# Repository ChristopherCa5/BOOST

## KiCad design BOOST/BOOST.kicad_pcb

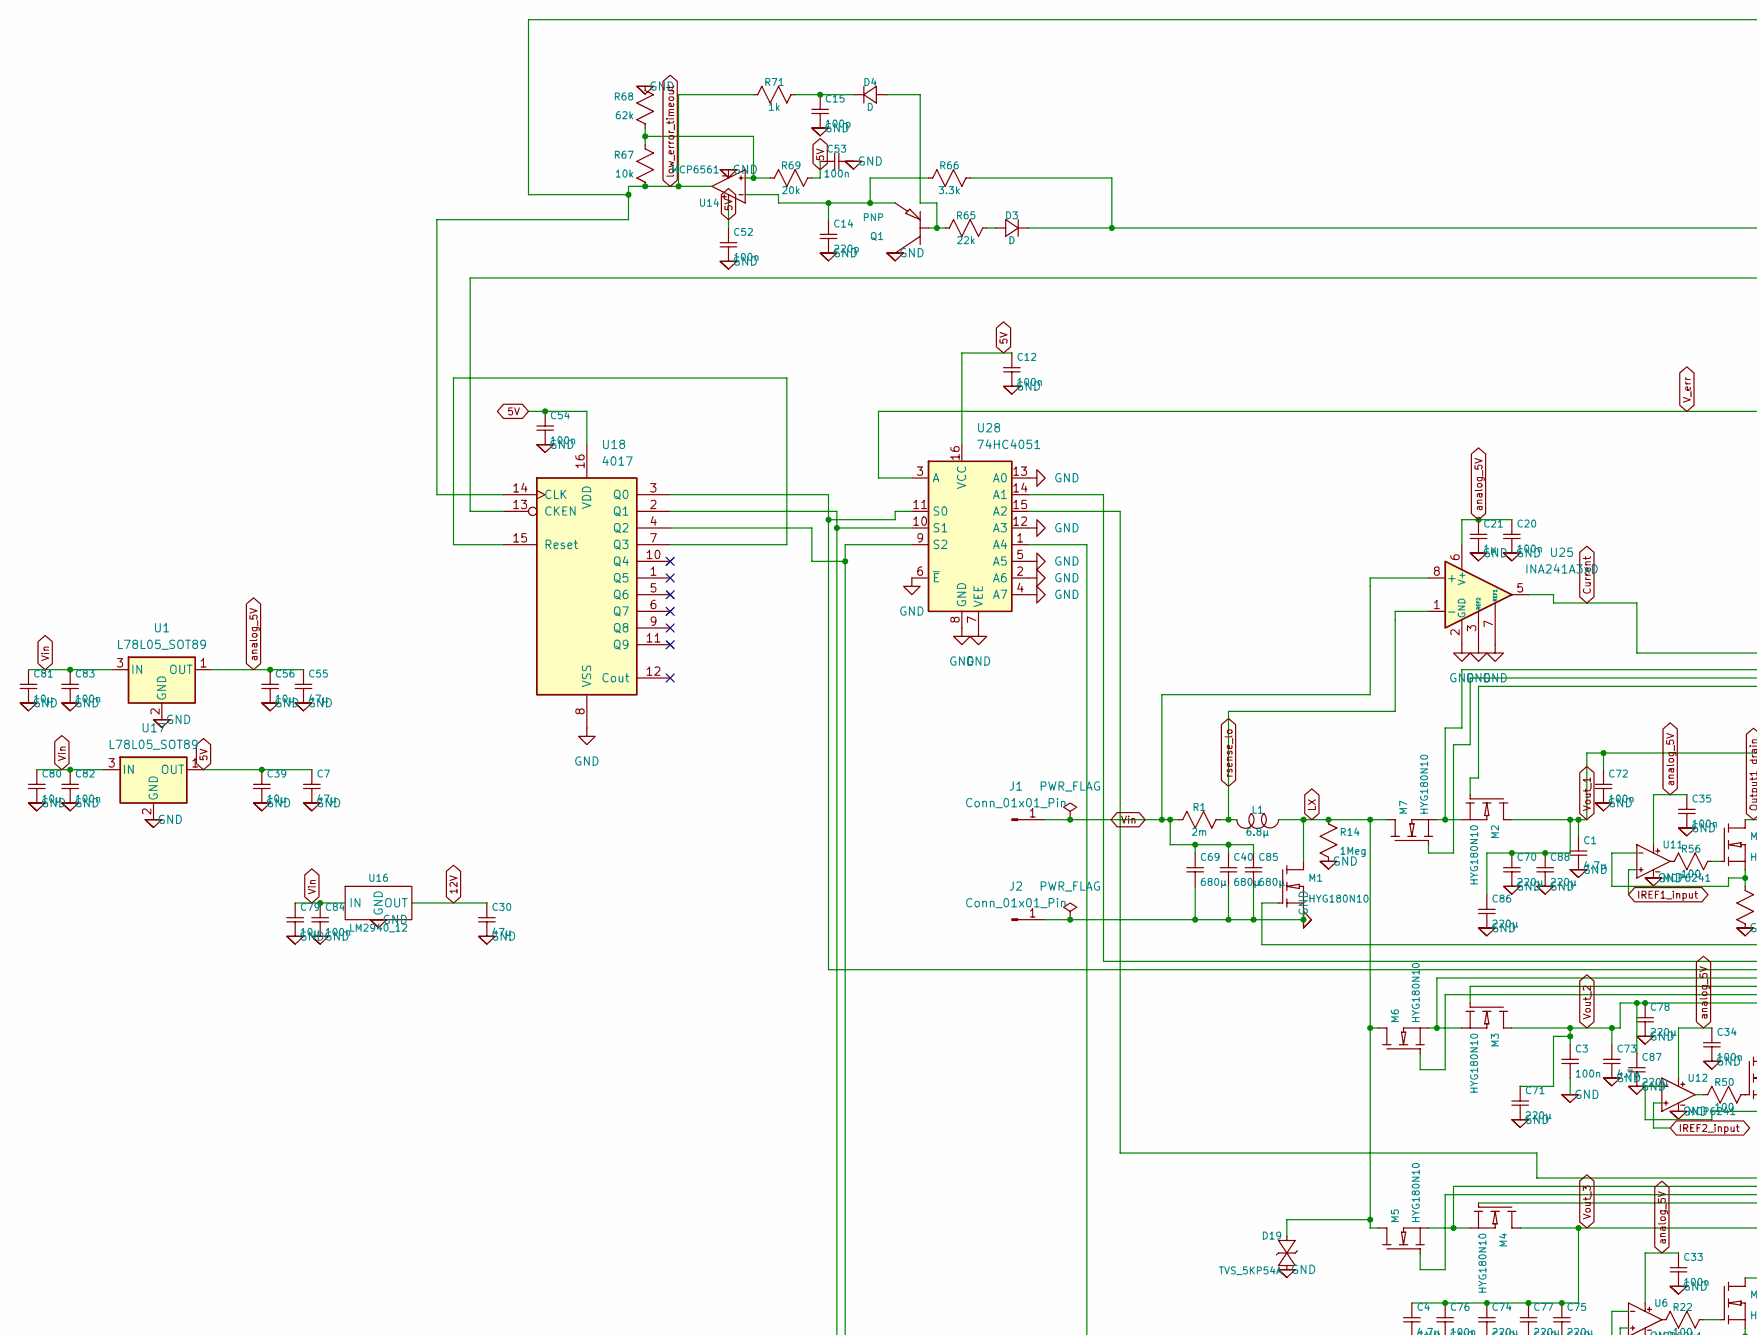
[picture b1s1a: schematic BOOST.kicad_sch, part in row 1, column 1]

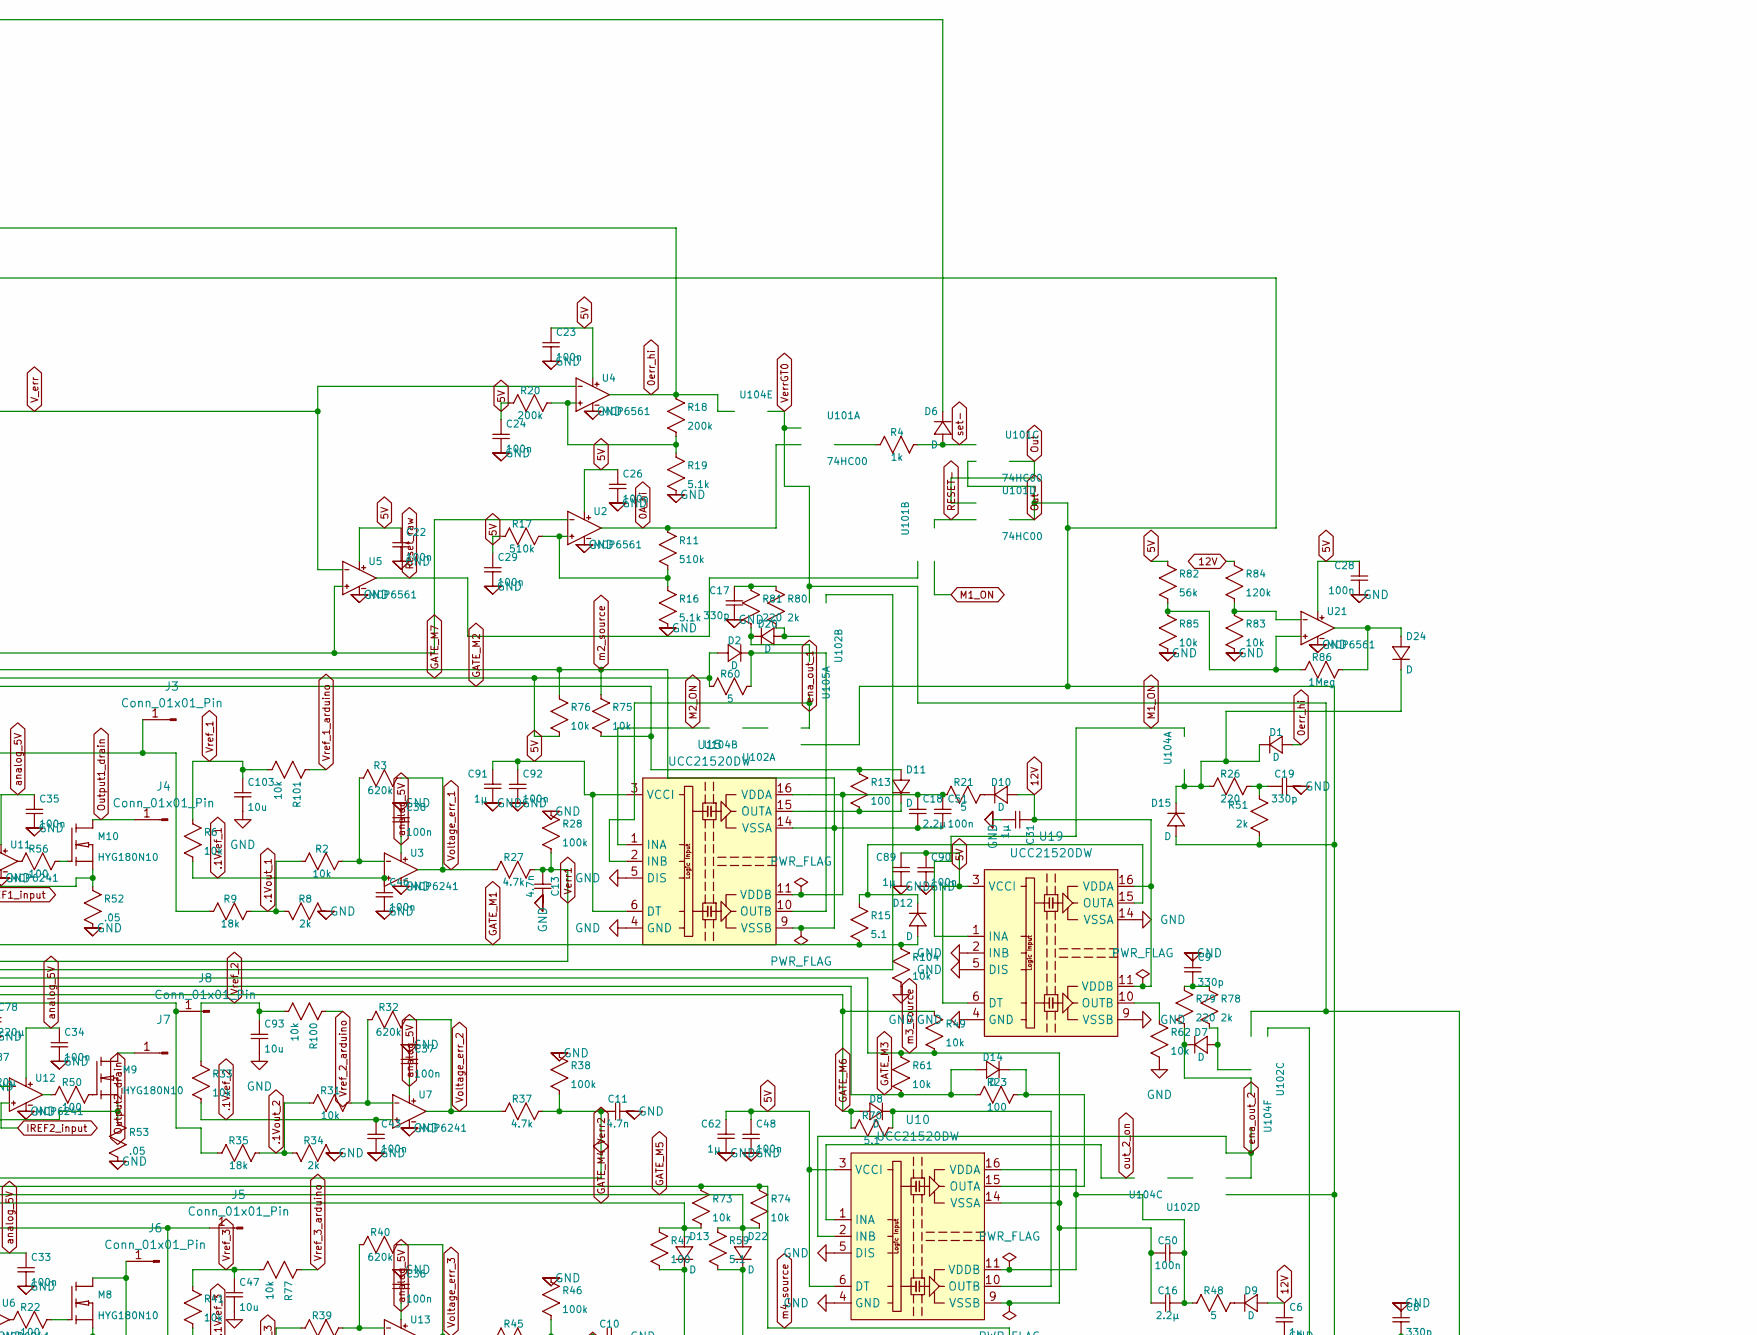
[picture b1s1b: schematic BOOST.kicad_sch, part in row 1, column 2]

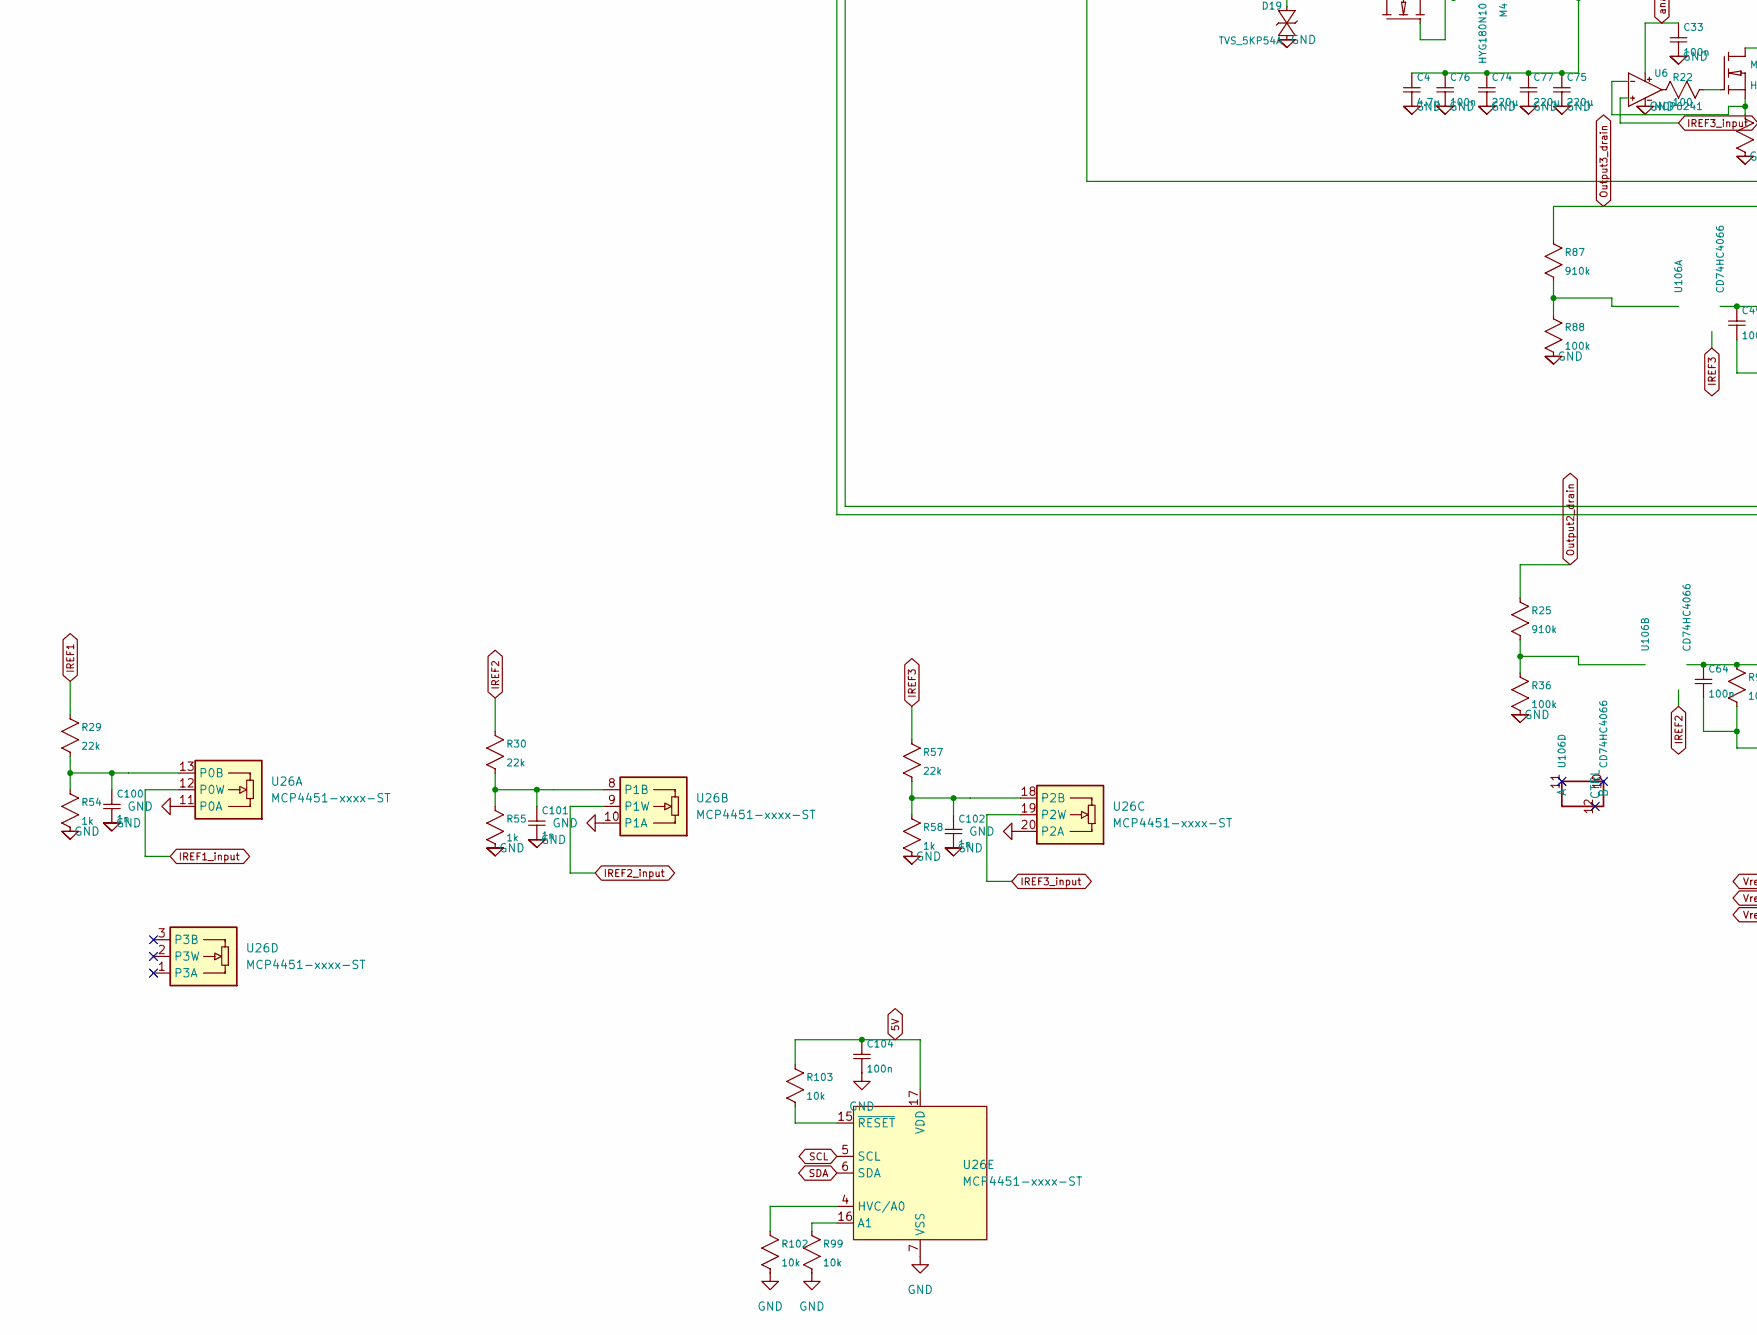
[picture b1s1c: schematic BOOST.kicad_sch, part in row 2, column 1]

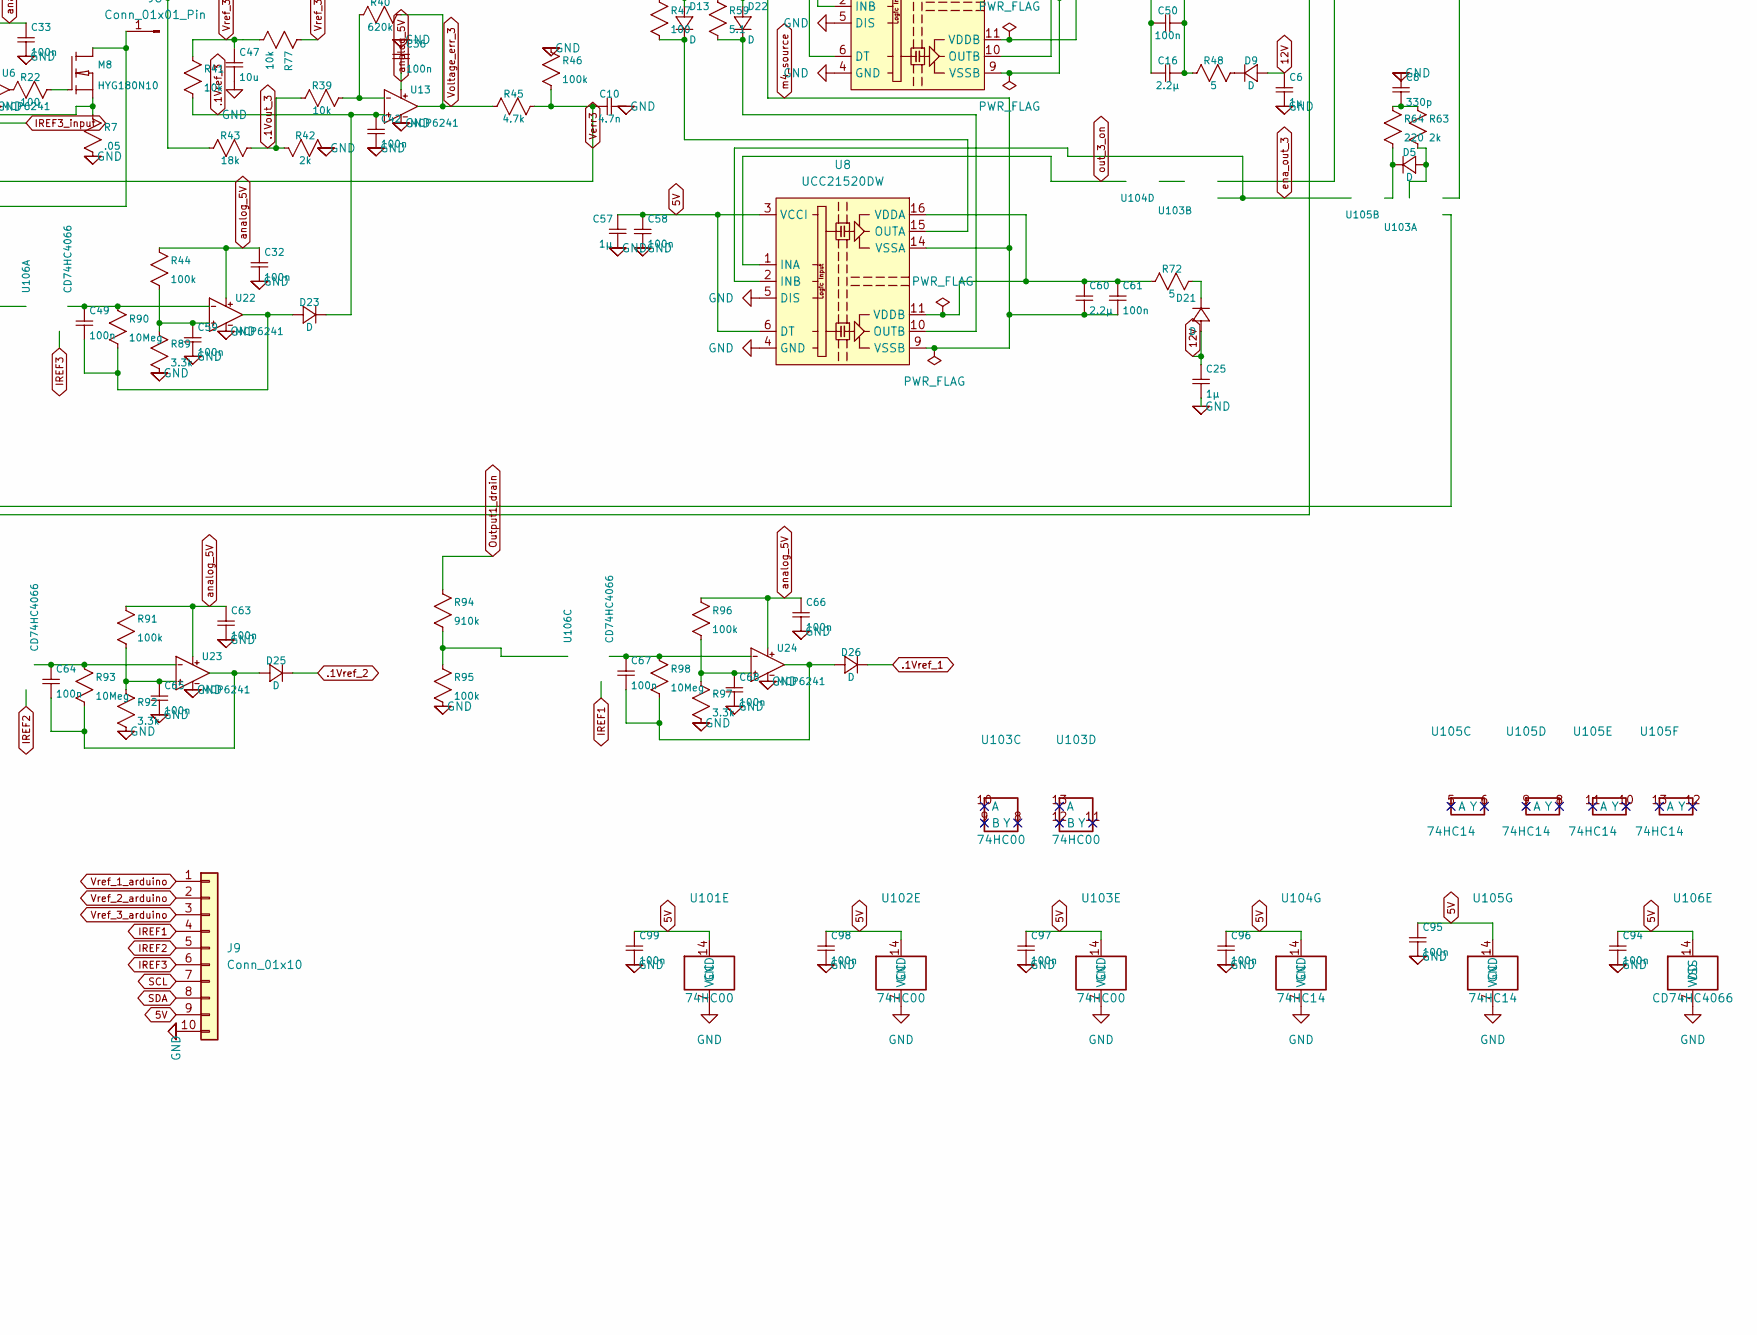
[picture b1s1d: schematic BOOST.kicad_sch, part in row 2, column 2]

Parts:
C1, C4, C73: 4.7µ; C_1210_3225Metric
C3, C72, C76: 100n; C_0805_2012Metric
C6, C21, C25, C31, C57, C62, C89, C91: 1µ; C_0805_2012Metric
C7, C30, C55: 47µ; CP_Elec_6.3x5.4
C8, C9, C17, C19: 330p; C_0603_1608Metric
C10, C11, C13: 4.7n; C_0603_1608Metric
C12, C20, C22, C23, C24, C26, C28, C29, C32, C33, C34, C35, C36, C37, C38, C42, C43, C46, C48, C50, C51, C52, C53, C54, C58, C59, C61, C63, C65, C66, C68, C82, C83, C84, C90, C92, C94, C95, C96, C97, C98, C99, C104: 100n; C_0603_1608Metric
C14: 220p; C_0603_1608Metric
C15: 100p; C_0603_1608Metric
C16, C18, C60: 2.2µ; C_1206_3216Metric
C39, C56, C79, C80, C81: 10µ; C_1210_3225Metric
C40, C69, C85: 680µ; CP_Elec_10x12.5
C47, C93, C103: 10u; C_0603_1608Metric
C49, C64, C67: 100n; C_1206_3216Metric
C70, C71, C74, C75, C77, C78, C86, C87, C88: 220µ; CP_Elec_10x10.5
C100, C101, C102: 1n; C_0603_1608Metric
D1, D2, D3, D4, D5, D6, D7, D8, D9, D10, D11, D12, D13, D14, D15, D20, D21, D22, D24: D; D_SOD-123
D19: TVS_5KP54A; D_SMC
D23, D25, D26: D; D_SOD-323
J1, J2: Conn_01x01_Pin; MountingHole_4.3mm_M4_Pad_TopBottom
J3, J4, J5, J6, J7, J8: Conn_01x01_Pin; TestPoint_THTPad_4.0x4.0mm_Drill2.0mm
J9: Conn_01x10; PinHeader_1x10_P2.54mm_Vertical
L1: 6.8µ; IND_CSCF3218-6R8MC
M1, M2, M3, M4, M5, M6, M7, M8, M9, M10: HYG180N10; TO-220-3_Horizontal_TabDown
Q1: PNP; SOT-23
R1: 2m; R_2512_6332Metric
R2, R6, R31, R33, R39, R41, R49, R61, R62, R67, R73, R74, R75, R76, R77, R83, R85, R99, R100, R101, R102, R103, R104: 10k; R_0603_1608Metric
R3, R32, R40: 620k; R_0603_1608Metric
R4, R54, R55, R58, R71: 1k; R_0603_1608Metric
R7, R52, R53: .05; R_2512_6332Metric
R8, R34, R42, R51, R63, R78, R80: 2k; R_0603_1608Metric
R9, R35, R43: 18k; R_0805_2012Metric
R11, R17: 510k; R_0603_1608Metric
R13, R22, R23, R47, R50, R56: 100; R_0603_1608Metric
R14, R86: 1Meg; R_0805_2012Metric
R15, R59, R70: 5.1; R_0805_2012Metric
R16, R19: 5.1k; R_0603_1608Metric
R18, R20: 200k; R_0603_1608Metric
R21, R48, R60, R72: 5; R_0805_2012Metric
R25, R87, R94: 910k; R_0805_2012Metric
R26, R64, R79, R81: 220; R_0603_1608Metric
R27, R37, R45: 4.7k; R_0603_1608Metric
R28, R36, R38, R44, R46, R88, R91, R95, R96: 100k; R_0603_1608Metric
R29, R30, R57: 22k; R_0805_2012Metric
R65: 22k; R_0603_1608Metric
R66, R89, R92, R97: 3.3k; R_0603_1608Metric
R68: 62k; R_0603_1608Metric
R69: 20k; R_0603_1608Metric
R82: 56k; R_0603_1608Metric
R84: 120k; R_0603_1608Metric
R90, R93, R98: 10Meg; R_0603_1608Metric
U1, U17: L78L05_SOT89; SOT-89-3
U2, U4, U5, U14, U21: MCP6561; SOT-23-5
U3, U6, U7, U11, U12, U13, U22, U23, U24: MCP6241; SOT-23-5
U8, U10, U15, U19: UCC21520DW; SOIC-16W_7.5x10.3mm_P1.27mm
U16: LM2940_12; TO-263-3_TabPin2
U18: 4017; SOIC-16_3.9x9.9mm_P1.27mm
U25: INA241A3xD; SOIC-8_3.9x4.9mm_P1.27mm
U26: MCP4451-xxxx-ST; TSSOP-20_4.4x6.5mm_P0.65mm
U28: 74HC4051; SOIC-16_3.9x9.9mm_P1.27mm
U101, U102, U103: 74HC00; SOIC-14_3.9x8.7mm_P1.27mm
U104, U105: 74HC14; SOIC-14_3.9x8.7mm_P1.27mm
U106: CD74HC4066; SOIC-14_3.9x8.7mm_P1.27mm

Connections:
0A_hi: R11.1, U2.1 (OUT), U101.2 (B)
0err_hi: D1.2 (+), D3.1 (-), R18.1, R66.1, U4.1 (OUT), U104.11 (A)
5V: C7.1, C12.1, C22.1, C23.1, C24.1, C26.1, C28.1, C29.1, C39.1, C48.1, C52.1, C53.2, C54.1, C57.2, C58.1, C62.2, C89.2, C90.1, C91.2, C92.1, C94.1, C95.1, C96.1, C97.1, C98.1, C99.1, C104.1, J9.9, R17.2, R20.2, R69.2, R82.1, R103.1, U2.5 (V+), U4.5 (V+), U5.5 (V+), U8.3 (VCCI), U8.6 (DT), U8.8 (VCCI), U10.3 (VCCI), U10.6 (DT), U10.8 (VCCI), U14.5 (V+), U15.3 (VCCI), U15.6 (DT), U15.8 (VCCI), U17.1 (OUT), U18.16 (VDD), U19.3 (VCCI), U19.6 (DT), U19.8 (VCCI), U21.5 (V+), U26.17 (VDD), U28.16 (VCC), U101.14 (VCC), U102.14 (VCC), U103.14 (VCC), U104.14 (VCC), U105.14 (VCC), U106.14 (VDD)
12V: C6.1, C25.1, C30.1, C31.1, D9.2 (+), D10.2 (+), D21.2 (+), R84.1, U16.3 (OUT), U19.11 (VDDB), U19.16 (VDDA)
.1Vout_1: R2.2, R8.1, R9.1
.1Vout_2: R31.2, R34.1, R35.1
.1Vout_3: R39.2, R42.1, R43.1
.1Vref_1: C46.1, D26.1 (-), R6.2, U3.3 (In+)
.1Vref_2: C43.1, D25.1 (-), R33.2, U7.3 (In+)
.1Vref_3: C42.1, D23.1 (-), R41.2, U13.3 (In+)
Current: U2.4 (In-), U5.3 (In+), U25.5
GATE_M1: D12.2 (+), M1.1 (G), R15.2, R104.1
GATE_M2: D11.2 (+), M2.1 (G), R13.1, R75.2
GATE_M3: D14.2 (+), M3.1 (G), R23.2, R61.2
GATE_M4: D13.2 (+), M4.1 (G), R47.1, R73.2
GATE_M5: D22.2 (+), M5.1 (G), R59.1, R74.2
GATE_M6: D8.2 (+), M6.1 (G), R49.1, R70.2
GATE_M7: D2.2 (+), M7.1 (G), R60.2, R76.2
GND: C1.2, C3.2, C4.2, C6.2, C7.2, C8.1, C9.1, C10.1, C11.1, C12.2, C13.1, C14.2, C15.2, C17.1, C19.2, C20.2, C21.2, C22.2, C23.2, C24.2, C25.2, C26.2, C28.2, C29.2, C30.2, C31.2, C32.2, C33.2, C34.2, C35.2, C36.1, C37.1, C38.1, C39.2, C40.2, C42.2, C43.2, C46.2, C47.2, C48.2, C52.2, C53.1, C54.2, C55.2, C56.2, C57.1, C58.2, C59.2, C62.1, C63.2, C65.2, C66.2, C68.2, C69.2, C70.2, C71.2, C72.2, C73.2, C74.2, C75.2, C76.2, C77.2, C78.2, C79.2, C80.2, C81.2, C82.2, C83.2, C84.2, C85.2, C86.2, C87.2, C88.2, C89.1, C90.2, C91.1, C92.2, C93.2, C94.2, C95.2, C96.2, C97.2, C98.2, C99.2, C100.2, C101.2, C102.2, C103.2, C104.2, D19.2 (+), J2.1 (Pin_1_1), J9.10, M1.3 (S), Q1.3 (C), R7.2, R8.2, R14.2, R16.2, R19.2, R28.1, R34.2, R36.2, R38.1, R42.2, R46.1, R52.2, R53.2, R54.2, R55.2, R58.2, R62.2, R68.2, R83.2, R85.2, R88.2, R89.2, R92.2, R95.2, R97.2, R99.2, R102.2, R104.2, U1.2 (GND), U2.2 (V-), U3.2 (V-), U4.2 (V-), U5.2 (V-), U6.2 (V-), U7.2 (V-), U8.4 (GND), U8.5 (DIS), U10.4 (GND), U10.5 (DIS), U11.2 (V-), U12.2 (V-), U13.2 (V-), U14.2 (V-), U15.4 (GND), U15.5 (DIS), U16.2 (GND), U17.2 (GND), U18.8 (VSS), U19.2 (INB), U19.4 (GND), U19.5 (DIS), U19.9 (VSSB), U19.14 (VSSA), U21.2 (V-), U22.2 (V-), U23.2 (V-), U24.2 (V-), U25.2 (GND), U25.3 (REF2), U25.4 (GND), U25.7 (REF1), U26.7 (VSS), U26.10 (P1A), U26.11 (P0A), U26.20 (P2A), U28.2 (A6), U28.4 (A7), U28.5 (A5), U28.6 (~E), U28.7 (VEE), U28.8 (GND), U28.12 (A3), U28.13 (A0), U101.7 (GND), U102.7 (GND), U103.7 (GND), U104.7 (GND), U105.7 (GND), U106.7 (VSS)
IREF1: J9.4, R29.1, U106.6 (CTRL)
IREF1_input: U11.3 (In+), U26.12 (P0W)
IREF2: J9.5, R30.1, U106.5 (CTRL)
IREF2_input: U12.3 (In+), U26.9 (P1W)
IREF3: J9.6, R57.1, U106.13 (CTRL)
IREF3_input: U6.3 (In+), U26.19 (P2W)
LX: D19.1 (-), L1.1, M1.2 (D), M5.2 (D), M6.2 (D), M7.2 (D), R14.1
M1_ON: U19.1 (INA), U101.5 (B), U104.2 (Y)
M2_ON: U15.1 (INA), U104.4 (Y)
unnamed: C8.2, R63.1, R64.1
unnamed: C9.2, R78.1, R79.1
unnamed: C17.2, R80.1, R81.1
unnamed: C19.1, R26.2, R51.2
unnamed: D1.1 (-), D15.1 (-), D24.1 (-), R26.1, U104.1 (A)
unnamed: D2.1 (-), R60.1, U15.10 (OUTB)
unnamed: D3.2 (+), R65.2
unnamed: D4.2 (+), Q1.1 (B), R65.1
unnamed: C15.1, D4.1 (-), R71.1
unnamed: D5.2 (+), R63.2, U103.3 (Y)
unnamed: D5.1 (-), R64.2, U105.3 (A)
unnamed: D7.2 (+), R78.2, U102.8 (Y)
unnamed: D7.1 (-), R79.2, U104.13 (A)
unnamed: D8.1 (-), R70.1, U10.10 (OUTB)
unnamed: D9.1 (-), R48.1
unnamed: D10.1 (-), R21.1
unnamed: D11.1 (-), R13.2, U15.15 (OUTA)
unnamed: D12.1 (-), R15.1, U19.15 (OUTA)
unnamed: D13.1 (-), R47.2, U8.15 (OUTA)
unnamed: D14.1 (-), R23.1, U10.15 (OUTA)
unnamed: D20.2 (+), R80.2, U102.6 (Y)
unnamed: D20.1 (-), R81.2, U105.1 (A)
unnamed: D21.1 (-), R72.1
unnamed: D22.1 (-), R59.2, U8.10 (OUTB)
unnamed: C49.2, D23.2 (+), R90.2, U22.1 (OUT)
unnamed: D24.2 (+), R86.1, U21.1 (OUT)
unnamed: C64.2, D25.2 (+), R93.2, U23.1 (OUT)
unnamed: C67.2, D26.2 (+), R98.2, U24.1 (OUT)
unnamed: M8.1 (G), R22.1
unnamed: M8.3 (S), R7.1, U6.4 (In-)
unnamed: M9.1 (G), R50.1
unnamed: M9.3 (S), R53.1, U12.4 (In-)
unnamed: M10.1 (G), R56.1
unnamed: M10.3 (S), R52.1, U11.4 (In-)
unnamed: C14.1, Q1.2 (E), R66.2, U14.4 (In-)
unnamed: R11.2, R16.1, R17.1, U2.3 (In+)
unnamed: R2.1, R3.2, U3.4 (In-)
unnamed: R18.2, R19.1, R20.1, U4.3 (In+)
unnamed: R22.2, U6.1 (OUT)
unnamed: R31.1, R32.2, U7.4 (In-)
unnamed: C60.1, C61.1, R72.2, U8.11 (VDDB), U8.16 (VDDA)
unnamed: C16.1, C50.1, R48.2, U10.11 (VDDB), U10.16 (VDDA)
unnamed: R56.2, U11.1 (OUT)
unnamed: R50.2, U12.1 (OUT)
unnamed: R39.1, R40.2, U13.4 (In-)
unnamed: R67.2, R68.1, R69.1, U14.3 (In+)
unnamed: C18.1, C51.1, R21.2, U15.11 (VDDB), U15.16 (VDDA)
unnamed: U18.7 (Q3), U18.15 (Reset)
unnamed: R62.1, U19.10 (OUTB)
unnamed: R82.2, R85.1, R86.2, U21.3 (In+)
unnamed: R83.1, R84.2, U21.4 (In-)
unnamed: C59.1, R44.2, R89.1, U22.3 (In+)
unnamed: C65.1, R91.2, R92.1, U23.3 (In+)
unnamed: C68.1, R96.2, R97.1, U24.3 (In+)
unnamed: C100.1, R29.2, R54.1, U26.13 (P0B)
unnamed: C101.1, R30.2, R55.1, U26.8 (P1B)
unnamed: C102.1, R57.2, R58.1, U26.18 (P2B)
unnamed: R99.1, U26.16 (A1)
unnamed: R102.1, U26.4 (HVC/A0)
unnamed: R103.2, U26.15 (~RESET)
unnamed: R4.2, U101.3 (Y)
unnamed: U102.3 (Y), U104.3 (A)
unnamed: U18.3 (Q0), U28.11 (S0), U102.4 (A)
unnamed: U18.2 (Q1), U28.10 (S1), U102.10 (A)
unnamed: U102.11 (Y), U104.5 (A)
unnamed: U18.4 (Q2), U28.9 (S2), U103.1 (A)
unnamed: U103.6 (Y), U104.9 (A)
unnamed: R87.2, R88.1, U106.1 (A)
unnamed: C49.1, R90.1, U22.4 (In-), U106.2 (B)
unnamed: R25.2, R36.1, U106.3 (A)
unnamed: C64.1, R93.1, U23.4 (In-), U106.4 (B)
unnamed: R94.2, R95.1, U106.8 (A)
unnamed: C67.1, R98.1, U24.4 (In-), U106.9 (B)
Out: U101.8 (Y), U101.13 (A)
Out-: D15.2 (+), R51.1, U18.13 (CKEN), U101.9 (B), U101.11 (Y), U102.1 (A), U102.13 (A), U103.5 (B)
Output1_drain: J4.1 (Pin_1_1), M10.2 (D), R94.1
Output2_drain: J7.1 (Pin_1_1), M9.2 (D), R25.1
Output3_drain: J6.1 (Pin_1_1), M8.2 (D), R87.1
RESET-: U101.6 (Y), U101.12 (B)
Reset_raw: U5.1 (OUT), U101.4 (A)
SCL: J9.7, U26.5 (SCL)
SDA: J9.8, U26.6 (SDA)
V_err: U4.4 (In-), U5.4 (In-), U28.3 (A)
Verr1: C13.2, R27.2, R28.2, U28.14 (A1)
Verr2: C11.2, R37.2, R38.2, U28.15 (A2)
Verr3: C10.2, R45.2, R46.2, U28.1 (A4)
VerrGT0: U101.1 (A), U102.5 (B), U102.9 (B), U103.2 (B), U104.10 (Y)
Vin: C40.1, C69.1, C79.1, C80.1, C81.1, C82.1, C83.1, C84.1, C85.1, J1.1 (Pin_1_1), R1.2, U1.3 (IN), U16.1 (IN), U17.3 (IN), U25.8 (+)
Voltage_err_1: R3.1, R27.1, U3.1 (OUT)
Voltage_err_2: R32.1, R37.1, U7.1 (OUT)
Voltage_err_3: R40.1, R45.1, U13.1 (OUT)
Vout_1: C1.1, C70.1, C72.1, C86.1, C88.1, J3.1 (Pin_1_1), M2.2 (D), R9.2
Vout_2: C3.1, C71.1, C73.1, C78.1, C87.1, J8.1 (Pin_1_1), M3.2 (D), R35.2
Vout_3: C4.1, C74.1, C75.1, C76.1, C77.1, J5.1 (Pin_1_1), M4.2 (D), R43.2
Vref_1: C103.1, R6.1, R101.2
Vref_1_arduino: J9.1, R101.1
Vref_2: C93.1, R33.1, R100.2
Vref_2_arduino: J9.2, R100.1
Vref_3: C47.1, R41.1, R77.2
Vref_3_arduino: J9.3, R77.1
analog_5V: C20.1, C21.1, C32.1, C33.1, C34.1, C35.1, C36.2, C37.2, C38.2, C55.1, C56.1, C63.1, C66.1, R44.1, R91.1, R96.1, U1.1 (OUT), U3.5 (V+), U6.5 (V+), U7.5 (V+), U11.5 (V+), U12.5 (V+), U13.5 (V+), U22.5 (V+), U23.5 (V+), U24.5 (V+), U25.6 (V+)
ena_out_1: U15.2 (INB), U102.2 (B), U105.2 (Y)
ena_out_2: U10.2 (INB), U102.12 (B), U104.12 (Y)
ena_out_3: U8.2 (INB), U103.4 (A), U105.4 (Y)
low_error_timeout: D6.1 (-), R67.1, R71.2, U14.1 (OUT), U18.14 (CLK)
m2_source: C18.2, C51.2, M2.3 (S), M7.3 (S), R75.1, R76.1, U15.9 (VSSB), U15.14 (VSSA)
m3_source: C16.2, C50.2, M3.3 (S), M6.3 (S), R49.2, R61.1, U10.9 (VSSB), U10.14 (VSSA)
m4_source: C60.2, C61.2, M4.3 (S), M5.3 (S), R73.1, R74.1, U8.9 (VSSB), U8.14 (VSSA)
out_2_on: U10.1 (INA), U104.6 (Y)
out_3_on: U8.1 (INA), U104.8 (Y)
rsense_lo: L1.2, R1.1, U25.1 (-)
set-: D6.2 (+), R4.1, U101.10 (A)

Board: 2 copper layers, 273 parts (0 on the bottom side), 140 nets, no tracks yet.
